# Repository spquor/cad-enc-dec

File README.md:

# cad-enc-dec
Многоканальная система сбора и передачи дифференциальных сигналов

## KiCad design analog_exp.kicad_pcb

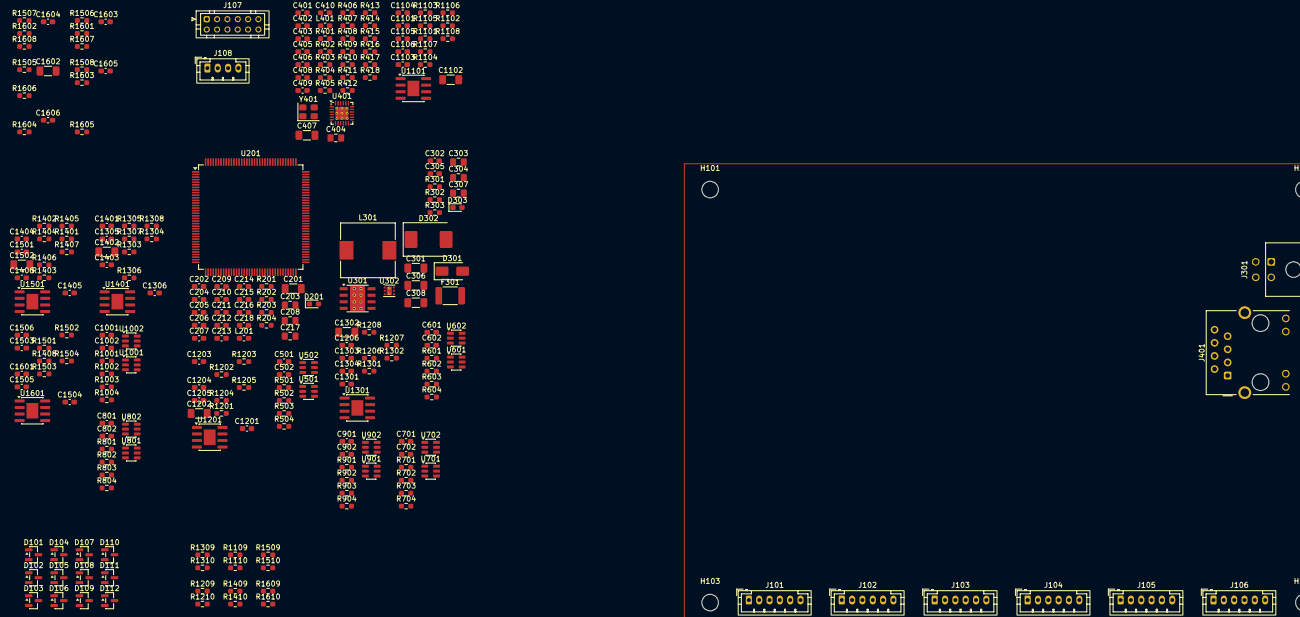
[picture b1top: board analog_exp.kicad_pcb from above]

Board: 2 copper layers, 250 parts (0 on the bottom side), 163 nets, no tracks yet.

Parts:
C201, C301, C407, C1102, C1202, C1302, C1402, C1502, C1602: 10uF; C_1206_3216Metric_Pad1.33x1.80mm_HandSolder
C202, C204, C205, C206, C207, C209, C210, C211, C212, C213, C214, C215, C216, C218, C305, C403, C406, C408, C409, C410, C501, C502, C601, C602, C701, C702, C801, C802, C901, C902, C1001, C1002, C1101, C1103, C1105, C1106, C1201, C1203, C1205, C1206, C1301, C1303, C1305, C1306, C1401, C1403, C1405, C1406, C1501, C1503, C1505, C1506, C1601, C1603, C1605, C1606: 100nF; C_0603_1608Metric_Pad1.08x0.95mm_HandSolder
C203, C208: 2.2uF; C_0805_2012Metric_Pad1.18x1.45mm_HandSolder
C217, C303, C304, C307, C404: 1uF; C_0805_2012Metric_Pad1.18x1.45mm_HandSolder
C302: 220nF; C_0603_1608Metric_Pad1.08x0.95mm_HandSolder
C306, C308: 22uF; C_1206_3216Metric_Pad1.33x1.80mm_HandSolder
C401, C402, C1104, C1204, C1304, C1404, C1504, C1604: 30pF; C_0603_1608Metric_Pad1.08x0.95mm_HandSolder
C405: 470pF; C_0603_1608Metric_Pad1.08x0.95mm_HandSolder
D101, D102, D103, D104, D105, D106, D107, D108, D109, D110, D111, D112: PESD12VL2BT; SOT-23
D201, D303: LED Blue; D_0603_1608Metric_Pad1.05x0.95mm_HandSolder
D301: SMAJ28CA; D_SMA
D302: SS54; D_SMC
F301: Fuse 24V 3A; Fuse_1812_4532Metric_Pad1.30x3.40mm_HandSolder
H101, H102, H103, H104: MountingHole; MountingHole_3.2mm_M3
J101, J102, J103, J104, J105, J106: JST PH B6B; JST_PH_B6B-PH-K_1x06_P2.00mm_Vertical
J107: JST PHD B12B; JST_PHD_B12B-PHDSS_2x06_P2.00mm_Vertical
J108: JST PH B4B; JST_PH_B4B-PH-K_1x04_P2.00mm_Vertical
J301: Power MX 3.0; Molex_Micro-Fit_3.0_43045-0400_2x02_P3.00mm_Horizontal
J401: HR911105A; RJ45_Hanrun_HR911105A_Horizontal
L201, L401: 600R@100Mhz; L_0603_1608Metric_Pad1.05x0.95mm_HandSolder
L301: 2.2uH; L_10.4x10.4_H4.8
R201, R417, R418: 270; R_0603_1608Metric_Pad0.98x0.95mm_HandSolder
R202, R203, R204, R406, R407, R408, R409, R410, R416, R1101, R1102, R1103, R1104, R1106, R1201, R1202, R1203, R1204, R1206, R1301, R1302, R1303, R1304, R1306, R1401, R1402, R1403, R1404, R1406, R1501, R1502, R1503, R1504, R1506, R1601, R1602, R1603, R1604, R1606: 10K; R_0603_1608Metric_Pad0.98x0.95mm_HandSolder
R301, R405: 1K5; R_0603_1608Metric_Pad0.98x0.95mm_HandSolder
R302: 100K; R_0603_1608Metric_Pad0.98x0.95mm_HandSolder
R303: 24K9; R_0603_1608Metric_Pad0.98x0.95mm_HandSolder
R401, R402, R403, R404: 10; R_0603_1608Metric_Pad0.98x0.95mm_HandSolder
R411, R412, R413, R415: 49.9; R_0603_1608Metric_Pad0.98x0.95mm_HandSolder
R414: 12K1; R_0603_1608Metric_Pad0.98x0.95mm_HandSolder
R501, R502, R503, R504, R601, R602, R603, R604, R701, R702, R703, R704, R801, R802, R803, R804, R901, R902, R903, R904, R1001, R1002, R1003, R1004, R1107, R1108, R1207, R1208, R1307, R1308, R1407, R1408, R1507, R1508, R1607, R1608: 0; R_0603_1608Metric_Pad0.98x0.95mm_HandSolder
R1105, R1205, R1305, R1405, R1505, R1605: 30K; R_0603_1608Metric_Pad0.98x0.95mm_HandSolder
R1109, R1110, R1209, R1210, R1309, R1310, R1409, R1410, R1509, R1510, R1609, R1610: 470; R_0603_1608Metric_Pad0.98x0.95mm_HandSolder
U201: STM32H723ZGT; LQFP-144_20x20mm_P0.5mm
U301: LMR33630B; Texas_HSOP-8-1EP_3.9x4.9mm_P1.27mm_ThermalVias
U302: TLV76733; WSON-6-1EP_2x2mm_P0.65mm_EP1x1.6mm_ThermalVias
U401: LAN8742AI; VQFN-24-1EP_4x4mm_P0.5mm_EP2.5x2.5mm_ThermalVias
U501, U502, U601, U602, U701, U702, U801, U802, U901, U902, U1001, U1002: INA600B; SOT-23-6
U1101, U1201, U1301, U1401, U1501, U1601: TSB582; SOIC-8-1EP_3.9x4.9mm_P1.27mm_EP2.29x3mm
Y401: ABM8G-25MHz; Crystal_SMD_3225-4Pin_3.2x2.5mm

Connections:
+3V3: C201.1, C202.1, C204.1, C205.1, C206.1, C207.1, C209.1, C210.1, C211.1, C212.1, C213.1, C214.1, C215.1, C216.1, C307.1, C403.1, D201.2 (A), J108.1, L201.2, L401.1, R202.1, R203.1, R204.1, R405.2, R406.2, R407.2, R408.2, R409.2, R1101.2, R1201.2, R1301.2, R1401.2, R1501.2, R1601.2, U201.6 (VBAT), U201.17 (VDD), U201.30 (VDD), U201.39 (VDD), U201.52 (VDD), U201.62 (VDD), U201.72 (VDD), U201.84 (VDD), U201.95 (VDD33USB), U201.108 (VDD), U201.121 (VDD), U201.131 (VDD), U201.144 (VDD), U302.1 (OUT), U302.2 (SNS), U401.9 (VDDIO)
+5V: C304.1, C306.1, C308.1, C501.2, C502.2, C601.2, C602.2, C701.2, C702.2, C801.2, C802.2, C901.2, C902.2, C1001.2, C1002.2, J107.1, J107.3, J107.5, J107.7, J107.9, J107.11, L301.2, R302.2, U302.4 (EN), U302.6 (IN), U501.6 (V+), U502.6 (V+), U601.6 (V+), U602.6 (V+), U701.6 (V+), U702.6 (V+), U801.6 (V+), U802.6 (V+), U901.6 (V+), U902.6 (V+), U1001.6 (V+), U1002.6 (V+), U1101.3 (+), U1101.5 (+), U1201.3 (+), U1201.5 (+), U1301.3 (+), U1301.5 (+), U1401.3 (+), U1401.5 (+), U1501.3 (+), U1501.5 (+), U1601.3 (+), U1601.5 (+)
+24V: C301.1, C302.1, C1102.2, C1103.2, C1202.2, C1203.2, C1302.2, C1303.2, C1402.2, C1403.2, C1502.2, C1503.2, C1602.2, C1603.2, D302.1 (K), D303.2 (A), F301.2, U301.2 (VIN), U301.3 (EN), U1101.8 (V+), U1201.8 (V+), U1301.8 (V+), U1401.8 (V+), U1501.8 (V+), U1601.8 (V+)
/Ethernet/CRS: R403.1, U201.43 (PA7)
/Ethernet/MDC: R408.1, U201.27 (PC1), U401.13 (MDC)
/Ethernet/MDIO: R405.1, U201.36 (PA2), U401.12 (MDIO)
/Ethernet/REFCLK: R404.1, U201.35 (PA1)
/Ethernet/RXD0: R401.1, U201.44 (PC4)
/Ethernet/RXD1: R402.1, U201.45 (PC5)
/Ethernet/TXD0: U201.73 (PB12), U401.17 (TXD0)
/Ethernet/TXD1: U201.74 (PB13), U401.18 (TXD1)
/Ethernet/TXEN: U201.70 (PB11), U401.16 (TXEN)
/Ethernet/nRST: U201.69 (PB10), U401.15 (~RST)
/GENOUT: C1101.1, C1201.1, C1301.1, C1401.1, C1501.1, C1601.1, R1101.1, R1102.2, R1201.1, R1202.2, R1301.1, R1302.2, R1401.1, R1402.2, R1501.1, R1502.2, R1601.1, R1602.2, U201.41 (PA5)
/RE1_COS: U201.20 (PF8), U502.1
/RE1_COS+: D102.1 (A1), J101.5, R503.1
/RE1_COS-: D102.2 (A2), J101.6, R504.1
/RE1_EXC+: J101.1, R1107.2, R1109.2
/RE1_EXC-: J101.2, R1108.2, R1110.2
/RE1_SIN: U201.19 (PF7), U501.1
/RE1_SIN+: D101.1 (A1), J101.3, R501.1
/RE1_SIN-: D101.2 (A2), J101.4, R502.1
/RE2_COS: U201.22 (PF10), U602.1
/RE2_COS+: D104.1 (A1), J102.5, R603.1
/RE2_COS-: D104.2 (A2), J102.6, R604.1
/RE2_EXC+: J102.1, R1207.2, R1209.2
/RE2_EXC-: J102.2, R1208.2, R1210.2
/RE2_SIN: U201.21 (PF9), U601.1
/RE2_SIN+: D103.1 (A1), J102.3, R601.1
/RE2_SIN-: D103.2 (A2), J102.4, R602.1
/RE3_COS: U201.26 (PC0), U702.1
/RE3_COS+: D106.1 (A1), J103.5, R703.1
/RE3_COS-: D106.2 (A2), J103.6, R704.1
/RE3_EXC+: J103.1, R1307.2, R1309.2
/RE3_EXC-: J103.2, R1308.2, R1310.2
/RE3_SIN: U201.34 (PA0), U701.1
/RE3_SIN+: D105.1 (A1), J103.3, R701.1
/RE3_SIN-: D105.2 (A2), J103.4, R702.1
/RE4_COS: U201.40 (PA4), U802.1
/RE4_COS+: D108.1 (A1), J104.5, R803.1
/RE4_COS-: D108.2 (A2), J104.6, R804.1
/RE4_EXC+: J104.1, R1407.2, R1409.2
/RE4_EXC-: J104.2, R1408.2, R1410.2
/RE4_SIN: U201.37 (PA3), U801.1
/RE4_SIN+: D107.1 (A1), J104.3, R801.1
/RE4_SIN-: D107.2 (A2), J104.4, R802.1
/RE5_COS: U201.47 (PB1), U902.1
/RE5_COS+: D110.1 (A1), J105.5, R903.1
/RE5_COS-: D110.2 (A2), J105.6, R904.1
/RE5_EXC+: J105.1, R1507.2, R1509.2
/RE5_EXC-: J105.2, R1508.2, R1510.2
/RE5_SIN: U201.46 (PB0), U901.1
/RE5_SIN+: D109.1 (A1), J105.3, R901.1
/RE5_SIN-: D109.2 (A2), J105.4, R902.1
/RE6_COS: U201.54 (PF14), U1002.1
/RE6_COS+: D112.1 (A1), J106.5, R1003.1
/RE6_COS-: D112.2 (A2), J106.6, R1004.1
/RE6_EXC+: J106.1, R1607.2, R1609.2
/RE6_EXC-: J106.2, R1608.2, R1610.2
/RE6_SIN: U201.53 (PF13), U1001.1
/RE6_SIN+: D111.1 (A1), J106.3, R1001.1
/RE6_SIN-: D111.2 (A2), J106.4, R1002.1
/SWDCLK: J108.2, U201.109 (PA14(JTCK)
/SWDIO: J108.3, U201.105 (PA13(JTMS)
/VREFOUT: U201.32 (VREF+), U501.5 (REF), U502.5 (REF), U601.5 (REF), U602.5 (REF), U701.5 (REF), U702.5 (REF), U801.5 (REF), U802.5 (REF), U901.5 (REF), U902.5 (REF), U1001.5 (REF), U1002.5 (REF)
GND: C201.2, C202.2, C203.2, C204.2, C205.2, C206.2, C207.2, C208.2, C209.2, C210.2, C211.2, C212.2, C213.2, C214.2, C215.2, C216.2, C217.2, C218.2, C301.2, C302.2, C303.2, C304.2, C306.2, C307.2, C308.2, C401.1, C402.1, C403.2, C404.2, C405.2, C406.2, C407.2, C408.2, C409.2, C410.2, C501.1, C502.1, C601.1, C602.1, C701.1, C702.1, C801.1, C802.1, C901.1, C902.1, C1001.1, C1002.1, C1102.1, C1103.1, C1105.1, C1106.1, C1202.1, C1203.1, C1205.1, C1206.1, C1302.1, C1303.1, C1305.1, C1306.1, C1402.1, C1403.1, C1405.1, C1406.1, C1502.1, C1503.1, C1505.1, C1506.1, C1602.1, C1603.1, C1605.1, C1606.1, D101.3 (common), D102.3 (common), D103.3 (common), D104.3 (common), D105.3 (common), D106.3 (common), D107.3 (common), D108.3 (common), D109.3 (common), D110.3 (common), D111.3 (common), D112.3 (common), D301.1 (A1), D302.2 (A), J107.2, J107.4, J107.6, J107.8, J107.10, J107.12, J108.4, J301.3, J301.4, J401.8, J401.SH, R201.1, R301.1, R303.1, R410.1, R414.1, R416.1, R417.1, R418.1, R1102.1, R1202.1, R1302.1, R1402.1, R1502.1, R1602.1, U201.16 (VSS), U201.31 (VSSA), U201.38 (VSS), U201.51 (VSS), U201.61 (VSS), U201.83 (VSS), U201.94 (VSS), U201.107 (VSS), U201.120 (VSS), U201.130 (VSS), U301.1 (GND), U301.9 (GND), U302.3 (GND), U302.5 (GND), U302.7 (PAD), U401.25 (VSS), U501.2 (GND), U502.2 (GND), U601.2 (GND), U602.2 (GND), U701.2 (GND), U702.2 (GND), U801.2 (GND), U802.2 (GND), U901.2 (GND), U902.2 (GND), U1001.2 (GND), U1002.2 (GND), U1101.4 (V-), U1201.4 (V-), U1301.4 (V-), U1401.4 (V-), U1501.4 (V-), U1601.4 (V-), Y401.2 (G), Y401.4 (G)
unnamed: C203.1, U201.71 (VCAP)
unnamed: C208.1, U201.106 (VCAP)
unnamed: C1101.2, R1103.1
unnamed: C1104.2, R1104.1, R1105.2, R1107.1, U1101.1
unnamed: C1105.2, R1109.1
unnamed: C1106.2, R1110.1
unnamed: C1201.2, R1203.1
unnamed: C1204.2, R1204.1, R1205.2, R1207.1, U1201.1
unnamed: C1205.2, R1209.1
unnamed: C1206.2, R1210.1
unnamed: C1301.2, R1303.1
unnamed: C1304.2, R1304.1, R1305.2, R1307.1, U1301.1
unnamed: C1305.2, R1309.1
unnamed: C1306.2, R1310.1
unnamed: C1401.2, R1403.1
unnamed: C1404.2, R1404.1, R1405.2, R1407.1, U1401.1
unnamed: C1405.2, R1409.1
unnamed: C1406.2, R1410.1
unnamed: C1501.2, R1503.1
unnamed: C1504.2, R1504.1, R1505.2, R1507.1, U1501.1
unnamed: C1505.2, R1509.1
unnamed: C1506.2, R1510.1
unnamed: C1601.2, R1603.1
unnamed: C1604.2, R1604.1, R1605.2, R1607.1, U1601.1
unnamed: C1605.2, R1609.1
unnamed: C1606.2, R1610.1
unnamed: D201.1 (K), R201.2
unnamed: D303.1 (K), R301.2
unnamed: J401.10, R417.2
unnamed: J401.11, R418.2
unnamed: C406.1, C407.1, C408.1, C409.1, C410.1, J401.4 (TCT), J401.5 (RCT), L401.2, R411.2, R412.2, R413.2, R415.2, U401.1 (VDD2A), U401.19 (VDD1A)
unnamed: J401.3 (RD+), R413.1, U401.23 (RXP)
unnamed: J401.6 (RD-), R415.1, U401.22 (RXN)
unnamed: J401.1 (TD+), R411.1, U401.21 (TXP)
unnamed: J401.2 (TD-), R412.1, U401.20 (TXN)
unnamed: R1106.2, R1108.1, U1101.7
unnamed: R1206.2, R1208.1, U1201.7
unnamed: R1306.2, R1308.1, U1301.7
unnamed: R1406.2, R1408.1, U1401.7
unnamed: R1506.2, R1508.1, U1501.7
unnamed: R1606.2, R1608.1, U1601.7
unnamed: R203.2, U201.138 (BOOT0)
unnamed: R202.2, U201.25 (NRST)
unnamed: R204.2, U201.143 (PDR_ON)
unnamed: C217.1, C218.1, L201.1, U201.33 (VDDA)
unnamed: C305.1, U301.7 (BOOT)
unnamed: R302.1, R303.2, U301.5 (FB)
unnamed: C305.2, L301.1, U301.8 (SW)
unnamed: C303.1, U301.6 (VCC)
unnamed: R403.2, U401.11 (CRS_DV/MODE2)
unnamed: J401.12, U401.3 (LED1/REGOFF)
unnamed: J401.9, R416.2, U401.2 (LED2/~INTSEL)
unnamed: R414.2, U401.24 (RBIAS)
unnamed: R401.2, R406.1, U401.8 (RXD0/MODE0)
unnamed: R402.2, R407.1, U401.7 (RXD1/MODE1)
unnamed: R410.2, U401.10 (RXER/PHYAD0)
unnamed: C404.1, C405.1, U401.6 (VDDCR)
unnamed: C401.2, U401.5 (XTAL1/CLKIN), Y401.3
unnamed: C402.2, U401.4 (XTAL2), Y401.1
unnamed: R404.2, R409.1, U401.14 (~INT/REFCLKO)
unnamed: R501.2, U501.3 (+)
unnamed: R502.2, U501.4 (-)
unnamed: R503.2, U502.3 (+)
unnamed: R504.2, U502.4 (-)
unnamed: R601.2, U601.3 (+)
unnamed: R602.2, U601.4 (-)
unnamed: R603.2, U602.3 (+)
unnamed: R604.2, U602.4 (-)
unnamed: R701.2, U701.3 (+)
unnamed: R702.2, U701.4 (-)
unnamed: R703.2, U702.3 (+)
unnamed: R704.2, U702.4 (-)
unnamed: R801.2, U801.3 (+)
unnamed: R802.2, U801.4 (-)
unnamed: R803.2, U802.3 (+)
unnamed: R804.2, U802.4 (-)
unnamed: R901.2, U901.3 (+)
unnamed: R902.2, U901.4 (-)
unnamed: R903.2, U902.3 (+)
unnamed: R904.2, U902.4 (-)
unnamed: R1001.2, U1001.3 (+)
unnamed: R1002.2, U1001.4 (-)
unnamed: R1003.2, U1002.3 (+)
unnamed: R1004.2, U1002.4 (-)
unnamed: C1104.1, R1103.2, R1105.1, U1101.2 (-)
unnamed: R1104.2, R1106.1, U1101.6 (-)
unnamed: C1204.1, R1203.2, R1205.1, U1201.2 (-)
unnamed: R1204.2, R1206.1, U1201.6 (-)
unnamed: C1304.1, R1303.2, R1305.1, U1301.2 (-)
unnamed: R1304.2, R1306.1, U1301.6 (-)
unnamed: C1404.1, R1403.2, R1405.1, U1401.2 (-)
unnamed: R1404.2, R1406.1, U1401.6 (-)
unnamed: C1504.1, R1503.2, R1505.1, U1501.2 (-)
unnamed: R1504.2, R1506.1, U1501.6 (-)
unnamed: C1604.1, R1603.2, R1605.1, U1601.2 (-)
unnamed: R1604.2, R1606.1, U1601.6 (-)
VDD: D301.2 (A2), F301.1, J301.1, J301.2

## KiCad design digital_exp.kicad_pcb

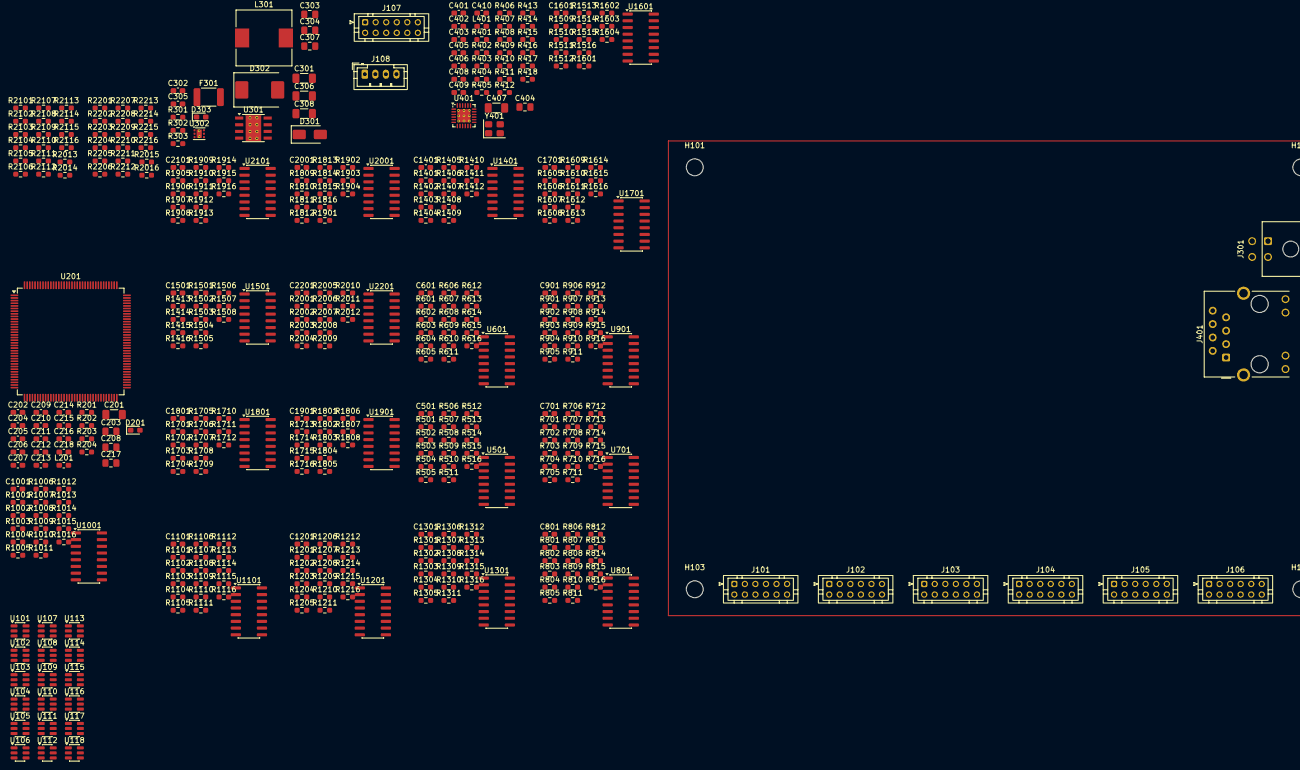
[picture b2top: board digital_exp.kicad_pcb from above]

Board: 2 copper layers, 430 parts (0 on the bottom side), 371 nets, no tracks yet.

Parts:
C201, C301, C407: 10uF; C_1206_3216Metric_Pad1.33x1.80mm_HandSolder
C202, C204, C205, C206, C207, C209, C210, C211, C212, C213, C214, C215, C216, C218, C305, C403, C406, C408, C409, C410, C501, C601, C701, C801, C901, C1001, C1101, C1201, C1301, C1401, C1501, C1601, C1701, C1801, C1901, C2001, C2101, C2201: 100nF; C_0603_1608Metric_Pad1.08x0.95mm_HandSolder
C203, C208: 2.2uF; C_0805_2012Metric_Pad1.18x1.45mm_HandSolder
C217, C303, C304, C307, C404: 1uF; C_0805_2012Metric_Pad1.18x1.45mm_HandSolder
C302: 220nF; C_0603_1608Metric_Pad1.08x0.95mm_HandSolder
C306, C308: 22uF; C_1206_3216Metric_Pad1.33x1.80mm_HandSolder
C401, C402: 30pF; C_0603_1608Metric_Pad1.08x0.95mm_HandSolder
C405: 470pF; C_0603_1608Metric_Pad1.08x0.95mm_HandSolder
D201, D303: LED Blue; D_0603_1608Metric_Pad1.05x0.95mm_HandSolder
D301: SMAJ28CA; D_SMA
D302: SS54; D_SMC
F301: Fuse 24V 3A; Fuse_1812_4532Metric_Pad1.30x3.40mm_HandSolder
H101, H102, H103, H104: MountingHole; MountingHole_3.2mm_M3
J101, J102, J103, J104, J105, J106, J107: JST PHD B12B; JST_PHD_B12B-PHDSS_2x06_P2.00mm_Vertical
J108: JST PH B4B; JST_PH_B4B-PH-K_1x04_P2.00mm_Vertical
J301: Power MX 3.0; Molex_Micro-Fit_3.0_43045-0400_2x02_P3.00mm_Horizontal
J401: HR911105A; RJ45_Hanrun_HR911105A_Horizontal
L201, L401: 600R@100Mhz; L_0603_1608Metric_Pad1.05x0.95mm_HandSolder
L301: 2.2uH; L_10.4x10.4_H4.8
R201, R417, R418: 270; R_0603_1608Metric_Pad0.98x0.95mm_HandSolder
R202, R203, R204, R406, R407, R408, R409, R410, R416, R1401, R1402, R1403, R1404, R1501, R1502, R1503, R1504, R1601, R1602, R1603, R1604, R1701, R1702, R1703, R1704, R1801, R1802, R1803, R1804, R1901, R1902, R1903, R1904, R2001, R2002, R2003, R2004, R2101, R2102, R2103, R2104, R2201, R2202, R2203, R2204: 10K; R_0603_1608Metric_Pad0.98x0.95mm_HandSolder
R301, R405: 1K5; R_0603_1608Metric_Pad0.98x0.95mm_HandSolder
R302: 100K; R_0603_1608Metric_Pad0.98x0.95mm_HandSolder
R303: 24K9; R_0603_1608Metric_Pad0.98x0.95mm_HandSolder
R401, R402, R403, R404, R505, R506, R507, R508, R509, R510, R511, R512, R605, R606, R607, R608, R609, R610, R611, R612, R705, R706, R707, R708, R709, R710, R711, R712, R805, R806, R807, R808, R809, R810, R811, R812, R905, R906, R907, R908, R909, R910, R911, R912, R1005, R1006, R1007, R1008, R1009, R1010, R1011, R1012, R1105, R1106, R1107, R1108, R1109, R1110, R1111, R1112, R1205, R1206, R1207, R1208, R1209, R1210, R1211, R1212, R1305, R1306, R1307, R1308, R1309, R1310, R1311, R1312, R1409, R1410, R1411, R1412, R1413, R1414, R1415, R1416, R1509, R1510, R1511, R1512, R1513, R1514, R1515, R1516, R1609, R1610, R1611, R1612, R1613, R1614, R1615, R1616, R1709, R1710, R1711, R1712, R1713, R1714, R1715, R1716, R1809, R1810, R1811, R1812, R1813, R1814, R1815, R1816, R1909, R1910, R1911, R1912, R1913, R1914, R1915, R1916, R2009, R2010, R2011, R2012, R2013, R2014, R2015, R2016, R2109, R2110, R2111, R2112, R2113, R2114, R2115, R2116, R2209, R2210, R2211, R2212, R2213, R2214, R2215, R2216: 10; R_0603_1608Metric_Pad0.98x0.95mm_HandSolder
R411, R412, R413, R415: 49.9; R_0603_1608Metric_Pad0.98x0.95mm_HandSolder
R414: 12K1; R_0603_1608Metric_Pad0.98x0.95mm_HandSolder
R501, R502, R503, R504, R601, R602, R603, R604, R701, R702, R703, R704, R801, R802, R803, R804, R901, R902, R903, R904, R1001, R1002, R1003, R1004, R1101, R1102, R1103, R1104, R1201, R1202, R1203, R1204, R1301, R1302, R1303, R1304: 100; R_0603_1608Metric_Pad0.98x0.95mm_HandSolder
R513, R514, R515, R516, R613, R614, R615, R616, R713, R714, R715, R716, R813, R814, R815, R816, R913, R914, R915, R916, R1013, R1014, R1015, R1016, R1113, R1114, R1115, R1116, R1213, R1214, R1215, R1216, R1313, R1314, R1315, R1316, R1405, R1406, R1407, R1408, R1505, R1506, R1507, R1508, R1605, R1606, R1607, R1608, R1705, R1706, R1707, R1708, R1805, R1806, R1807, R1808, R1905, R1906, R1907, R1908, R2005, R2006, R2007, R2008, R2105, R2106, R2107, R2108, R2205, R2206, R2207, R2208: 0R; R_0603_1608Metric_Pad0.98x0.95mm_HandSolder
U101, U102, U103, U104, U105, U106, U107, U108, U109, U110, U111, U112, U113, U114, U115, U116, U117, U118: SRV05-4; SOT-23-6
U201: STM32H723ZGT; LQFP-144_20x20mm_P0.5mm
U301: LMR33630B; Texas_HSOP-8-1EP_3.9x4.9mm_P1.27mm_ThermalVias
U302: TLV76733; WSON-6-1EP_2x2mm_P0.65mm_EP1x1.6mm_ThermalVias
U401: LAN8742AI; VQFN-24-1EP_4x4mm_P0.5mm_EP2.5x2.5mm_ThermalVias
U501, U601, U701, U801, U901, U1001, U1101, U1201, U1301: AM26LV32E; SOIC-16_3.9x9.9mm_P1.27mm
U1401, U1501, U1601, U1701, U1801, U1901, U2001, U2101, U2201: AM26LV31E; SOIC-16_3.9x9.9mm_P1.27mm
Y401: ABM8G-25MHz; Crystal_SMD_3225-4Pin_3.2x2.5mm

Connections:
+3V3: C201.1, C202.1, C204.1, C205.1, C206.1, C207.1, C209.1, C210.1, C211.1, C212.1, C213.1, C214.1, C215.1, C216.1, C307.1, C403.1, C501.2, C601.2, C701.2, C801.2, C901.2, C1001.2, C1101.2, C1201.2, C1301.2, C1401.2, C1501.2, C1601.2, C1701.2, C1801.2, C1901.2, C2001.2, C2101.2, C2201.2, D201.2 (A), J108.1, L201.2, L401.1, R202.1, R203.1, R204.1, R405.2, R406.2, R407.2, R408.2, R409.2, U201.6 (VBAT), U201.17 (VDD), U201.30 (VDD), U201.39 (VDD), U201.52 (VDD), U201.62 (VDD), U201.72 (VDD), U201.84 (VDD), U201.95 (VDD33USB), U201.108 (VDD), U201.121 (VDD), U201.131 (VDD), U201.144 (VDD), U302.1 (OUT), U302.2 (SNS), U401.9 (VDDIO), U501.4 (G), U501.16 (VDD), U601.4 (G), U601.16 (VDD), U701.4 (G), U701.16 (VDD), U801.4 (G), U801.16 (VDD), U901.4 (G), U901.16 (VDD), U1001.4 (G), U1001.16 (VDD), U1101.4 (G), U1101.16 (VDD), U1201.4 (G), U1201.16 (VDD), U1301.4 (G), U1301.16 (VDD), U1401.4 (G), U1401.16 (VDD), U1501.4 (G), U1501.16 (VDD), U1601.4 (G), U1601.16 (VDD), U1701.4 (G), U1701.16 (VDD), U1801.4 (G), U1801.16 (VDD), U1901.4 (G), U1901.16 (VDD), U2001.4 (G), U2001.16 (VDD), U2101.4 (G), U2101.16 (VDD), U2201.4 (G), U2201.16 (VDD)
+5V: C304.1, C306.1, C308.1, J107.1, J107.3, J107.5, J107.7, J107.9, J107.11, L301.2, R302.2, U302.4 (EN), U302.6 (IN)
+24V: C301.1, C302.1, D302.1 (K), D303.2 (A), F301.2, U301.2 (VIN), U301.3 (EN)
/EN1_A: R513.2, R1401.2, R1405.1, U201.15 (PF5)
/EN1_A+: J101.1, R501.1, R505.1, R1409.2, U101.1 (IO1)
/EN1_A-: J101.2, R501.2, R506.1, R1410.2, U101.4 (IO3)
/EN1_B: R514.2, R1402.2, R1406.1, U201.14 (PF4)
/EN1_B+: J101.3, R502.1, R507.1, R1411.2, U101.3 (IO2)
/EN1_B-: J101.4, R502.2, R508.1, R1412.2, U101.6 (IO4)
/EN1_U: R516.2, R1404.2, R1408.1, U201.12 (PF2)
/EN1_U+: J101.7, R504.1, R511.1, R1415.2, U110.3 (IO2)
/EN1_U-: J101.8, R504.2, R512.1, R1416.2, U110.6 (IO4)
/EN1_V: R613.2, R1501.2, R1505.1, U201.11 (PF1)
/EN1_V+: J101.9, R601.1, R605.1, R1509.2, U102.1 (IO1)
/EN1_V-: J101.10, R601.2, R606.1, R1510.2, U102.4 (IO3)
/EN1_W: R614.2, R1502.2, R1506.1, U201.10 (PF0)
/EN1_W+: J101.11, R602.1, R607.1, R1511.2, U102.3 (IO2)
/EN1_W-: J101.12, R602.2, R608.1, R1512.2, U102.6 (IO4)
/EN1_Z: R515.2, R1403.2, R1407.1, U201.13 (PF3)
/EN1_Z+: J101.5, R503.1, R509.1, R1413.2, U110.1 (IO1)
/EN1_Z-: J101.6, R503.2, R510.1, R1414.2, U110.4 (IO3)
/EN2_A: R615.2, R1503.2, R1507.1, U201.59 (PE8)
/EN2_A+: J102.1, R603.1, R609.1, R1513.2, U111.1 (IO1)
/EN2_A-: J102.2, R603.2, R610.1, R1514.2, U111.4 (IO3)
/EN2_B: R616.2, R1504.2, R1508.1, U201.63 (PE10)
/EN2_B+: J102.3, R604.1, R611.1, R1515.2, U111.3 (IO2)
/EN2_B-: J102.4, R604.2, R612.1, R1516.2, U111.6 (IO4)
/EN2_U: R714.2, R1602.2, R1606.1, U201.66 (PE13)
/EN2_U+: J102.7, R702.1, R707.1, R1611.2, U103.3 (IO2)
/EN2_U-: J102.8, R702.2, R708.1, R1612.2, U103.6 (IO4)
/EN2_V: R715.2, R1603.2, R1607.1, U201.60 (PE9)
/EN2_V+: J102.9, R703.1, R709.1, R1613.2, U112.1 (IO1)
/EN2_V-: J102.10, R703.2, R710.1, R1614.2, U112.4 (IO3)
/EN2_W: R716.2, R1604.2, R1608.1, U201.64 (PE11)
/EN2_W+: J102.11, R704.1, R711.1, R1615.2, U112.3 (IO2)
/EN2_W-: J102.12, R704.2, R712.1, R1616.2, U112.6 (IO4)
/EN2_Z: R713.2, R1601.2, R1605.1, U201.65 (PE12)
/EN2_Z+: J102.5, R701.1, R705.1, R1609.2, U103.1 (IO1)
/EN2_Z-: J102.6, R701.2, R706.1, R1610.2, U103.4 (IO3)
/EN3_A: R813.2, R1701.2, R1705.1, U201.77 (PD8)
/EN3_A+: J103.1, R801.1, R805.1, R1709.2, U104.1 (IO1)
/EN3_A-: J103.2, R801.2, R806.1, R1710.2, U104.4 (IO3)
/EN3_B: R814.2, R1702.2, R1706.1, U201.78 (PD9)
/EN3_B+: J103.3, R802.1, R807.1, R1711.2, U104.3 (IO2)
/EN3_B-: J103.4, R802.2, R808.1, R1712.2, U104.6 (IO4)
/EN3_U: R816.2, R1704.2, R1708.1, U201.80 (PD11)
/EN3_U+: J103.7, R804.1, R811.1, R1715.2, U113.3 (IO2)
/EN3_U-: J103.8, R804.2, R812.1, R1716.2, U113.6 (IO4)
/EN3_V: R913.2, R1801.2, R1805.1, U201.81 (PD12)
/EN3_V+: J103.9, R901.1, R905.1, R1809.2, U105.1 (IO1)
/EN3_V-: J103.10, R901.2, R906.1, R1810.2, U105.4 (IO3)
/EN3_W: R914.2, R1802.2, R1806.1, U201.82 (PD13)
/EN3_W+: J103.11, R902.1, R907.1, R1811.2, U105.3 (IO2)
/EN3_W-: J103.12, R902.2, R908.1, R1812.2, U105.6 (IO4)
/EN3_Z: R815.2, R1703.2, R1707.1, U201.79 (PD10)
/EN3_Z+: J103.5, R803.1, R809.1, R1713.2, U113.1 (IO1)
/EN3_Z-: J103.6, R803.2, R810.1, R1714.2, U113.4 (IO3)
/EN4_A: R915.2, R1803.2, R1807.1, U201.90 (PG5)
/EN4_A+: J104.1, R903.1, R909.1, R1813.2, U114.1 (IO1)
/EN4_A-: J104.2, R903.2, R910.1, R1814.2, U114.4 (IO3)
/EN4_B: R916.2, R1804.2, R1808.1, U201.91 (PG6)
/EN4_B+: J104.3, R904.1, R911.1, R1815.2, U114.3 (IO2)
/EN4_B-: J104.4, R904.2, R912.1, R1816.2, U114.6 (IO4)
/EN4_U: R1014.2, R1902.2, R1906.1, U201.93 (PG8)
/EN4_U+: J104.7, R1002.1, R1007.1, R1911.2, U106.3 (IO2)
/EN4_U-: J104.8, R1002.2, R1008.1, R1912.2, U106.6 (IO4)
/EN4_V: R1015.2, R1903.2, R1907.1, U201.96 (PC6)
/EN4_V+: J104.9, R1003.1, R1009.1, R1913.2, U115.1 (IO1)
/EN4_V-: J104.10, R1003.2, R1010.1, R1914.2, U115.4 (IO3)
/EN4_W: R1016.2, R1904.2, R1908.1, U201.97 (PC7)
/EN4_W+: J104.11, R1004.1, R1011.1, R1915.2, U115.3 (IO2)
/EN4_W-: J104.12, R1004.2, R1012.1, R1916.2, U115.6 (IO4)
/EN4_Z: R1013.2, R1901.2, R1905.1, U201.92 (PG7)
/EN4_Z+: J104.5, R1001.1, R1005.1, R1909.2, U106.1 (IO1)
/EN4_Z-: J104.6, R1001.2, R1006.1, R1910.2, U106.4 (IO3)
/EN5_A: R1113.2, R2001.2, R2005.1, U201.111 (PC10)
/EN5_A+: J105.1, R1101.1, R1105.1, R2009.2, U107.1 (IO1)
/EN5_A-: J105.2, R1101.2, R1106.1, R2010.2, U107.4 (IO3)
/EN5_B: R1114.2, R2002.2, R2006.1, U201.112 (PC11)
/EN5_B+: J105.3, R1102.1, R1107.1, R2011.2, U107.3 (IO2)
/EN5_B-: J105.4, R1102.2, R1108.1, R2012.2, U107.6 (IO4)
/EN5_U: R1116.2, R2004.2, R2008.1, U201.115 (PD1)
/EN5_U+: J105.7, R1104.1, R1111.1, R2015.2, U116.3 (IO2)
/EN5_U-: J105.8, R1104.2, R1112.1, R2016.2, U116.6 (IO4)
/EN5_V: R1213.2, R2101.2, R2105.1, U201.110 (PA15(JTDI))
/EN5_V+: J105.9, R1201.1, R1205.1, R2109.2, U108.1 (IO1)
/EN5_V-: J105.10, R1201.2, R1206.1, R2110.2, U108.4 (IO3)
/EN5_W: R1214.2, R2102.2, R2106.1, U201.133 (PB3(JTDO)
/EN5_W+: J105.11, R1202.1, R1207.1, R2111.2, U108.3 (IO2)
/EN5_W-: J105.12, R1202.2, R1208.1, R2112.2, U108.6 (IO4)
/EN5_Z: R1115.2, R2003.2, R2007.1, U201.114 (PD0)
/EN5_Z+: J105.5, R1103.1, R1109.1, R2013.2, U116.1 (IO1)
/EN5_Z-: J105.6, R1103.2, R1110.1, R2014.2, U116.4 (IO3)
/EN6_A: R1215.2, R2103.2, R2107.1, U201.125 (PG10)
/EN6_A+: J106.1, R1203.1, R1209.1, R2113.2, U117.1 (IO1)
/EN6_A-: J106.2, R1203.2, R1210.1, R2114.2, U117.4 (IO3)
/EN6_B: R1216.2, R2104.2, R2108.1, U201.126 (PG11)
/EN6_B+: J106.3, R1204.1, R1211.1, R2115.2, U117.3 (IO2)
/EN6_B-: J106.4, R1204.2, R1212.1, R2116.2, U117.6 (IO4)
/EN6_U: R1314.2, R2202.2, R2206.1, U201.128 (PG13)
/EN6_U+: J106.7, R1302.1, R1307.1, R2211.2, U109.3 (IO2)
/EN6_U-: J106.8, R1302.2, R1308.1, R2212.2, U109.6 (IO4)
/EN6_V: R1315.2, R2203.2, R2207.1, U201.134 (PB4(NJTRST))
/EN6_V+: J106.9, R1303.1, R1309.1, R2213.2, U118.1 (IO1)
/EN6_V-: J106.10, R1303.2, R1310.1, R2214.2, U118.4 (IO3)
/EN6_W: R1316.2, R2204.2, R2208.1, U201.135 (PB5)
/EN6_W+: J106.11, R1304.1, R1311.1, R2215.2, U118.3 (IO2)
/EN6_W-: J106.12, R1304.2, R1312.1, R2216.2, U118.6 (IO4)
/EN6_Z: R1313.2, R2201.2, R2205.1, U201.127 (PG12)
/EN6_Z+: J106.5, R1301.1, R1305.1, R2209.2, U109.1 (IO1)
/EN6_Z-: J106.6, R1301.2, R1306.1, R2210.2, U109.4 (IO3)
/Ethernet/CRS: R403.1, U201.43 (PA7)
/Ethernet/MDC: R408.1, U201.27 (PC1), U401.13 (MDC)
/Ethernet/MDIO: R405.1, U201.36 (PA2), U401.12 (MDIO)
/Ethernet/REFCLK: R404.1, U201.35 (PA1)
/Ethernet/RXD0: R401.1, U201.44 (PC4)
/Ethernet/RXD1: R402.1, U201.45 (PC5)
/Ethernet/TXD0: U201.73 (PB12), U401.17 (TXD0)
/Ethernet/TXD1: U201.74 (PB13), U401.18 (TXD1)
/Ethernet/TXEN: U201.70 (PB11), U401.16 (TXEN)
/Ethernet/nRST: U201.69 (PB10), U401.15 (~RST)
/SWDCLK: J108.2, U201.109 (PA14(JTCK)
/SWDIO: J108.3, U201.105 (PA13(JTMS)
GND: C201.2, C202.2, C203.2, C204.2, C205.2, C206.2, C207.2, C208.2, C209.2, C210.2, C211.2, C212.2, C213.2, C214.2, C215.2, C216.2, C217.2, C218.2, C301.2, C302.2, C303.2, C304.2, C306.2, C307.2, C308.2, C401.1, C402.1, C403.2, C404.2, C405.2, C406.2, C407.2, C408.2, C409.2, C410.2, C501.1, C601.1, C701.1, C801.1, C901.1, C1001.1, C1101.1, C1201.1, C1301.1, C1401.1, C1501.1, C1601.1, C1701.1, C1801.1, C1901.1, C2001.1, C2101.1, C2201.1, D301.1 (A1), D302.2 (A), J107.2, J107.4, J107.6, J107.8, J107.10, J107.12, J108.4, J301.3, J301.4, J401.8, J401.SH, R201.1, R301.1, R303.1, R410.1, R414.1, R416.1, R417.1, R418.1, R1401.1, R1402.1, R1403.1, R1404.1, R1501.1, R1502.1, R1503.1, R1504.1, R1601.1, R1602.1, R1603.1, R1604.1, R1701.1, R1702.1, R1703.1, R1704.1, R1801.1, R1802.1, R1803.1, R1804.1, R1901.1, R1902.1, R1903.1, R1904.1, R2001.1, R2002.1, R2003.1, R2004.1, R2101.1, R2102.1, R2103.1, R2104.1, R2201.1, R2202.1, R2203.1, R2204.1, U101.2 (VN), U102.2 (VN), U103.2 (VN), U104.2 (VN), U105.2 (VN), U106.2 (VN), U107.2 (VN), U108.2 (VN), U109.2 (VN), U110.2 (VN), U111.2 (VN), U112.2 (VN), U113.2 (VN), U114.2 (VN), U115.2 (VN), U116.2 (VN), U117.2 (VN), U118.2 (VN), U201.16 (VSS), U201.31 (VSSA), U201.38 (VSS), U201.51 (VSS), U201.61 (VSS), U201.83 (VSS), U201.94 (VSS), U201.107 (VSS), U201.120 (VSS), U201.130 (VSS), U301.1 (GND), U301.9 (GND), U302.3 (GND), U302.5 (GND), U302.7 (PAD), U401.25 (VSS), U501.8 (GND), U501.12 (~G), U601.8 (GND), U601.12 (~G), U701.8 (GND), U701.12 (~G), U801.8 (GND), U801.12 (~G), U901.8 (GND), U901.12 (~G), U1001.8 (GND), U1001.12 (~G), U1101.8 (GND), U1101.12 (~G), U1201.8 (GND), U1201.12 (~G), U1301.8 (GND), U1301.12 (~G), U1401.8 (GND), U1401.12 (~G), U1501.8 (GND), U1501.12 (~G), U1601.8 (GND), U1601.12 (~G), U1701.8 (GND), U1701.12 (~G), U1801.8 (GND), U1801.12 (~G), U1901.8 (GND), U1901.12 (~G), U2001.8 (GND), U2001.12 (~G), U2101.8 (GND), U2101.12 (~G), U2201.8 (GND), U2201.12 (~G), Y401.2 (G), Y401.4 (G)
unnamed: C203.1, U201.71 (VCAP)
unnamed: C208.1, U201.106 (VCAP)
unnamed: D201.1 (K), R201.2
unnamed: D303.1 (K), R301.2
unnamed: J401.10, R417.2
unnamed: J401.11, R418.2
unnamed: C406.1, C407.1, C408.1, C409.1, C410.1, J401.4 (TCT), J401.5 (RCT), L401.2, R411.2, R412.2, R413.2, R415.2, U401.1 (VDD2A), U401.19 (VDD1A)
unnamed: J401.3 (RD+), R413.1, U401.23 (RXP)
unnamed: J401.6 (RD-), R415.1, U401.22 (RXN)
unnamed: J401.1 (TD+), R411.1, U401.21 (TXP)
unnamed: J401.2 (TD-), R412.1, U401.20 (TXN)
unnamed: R203.2, U201.138 (BOOT0)
unnamed: R202.2, U201.25 (NRST)
unnamed: R204.2, U201.143 (PDR_ON)
unnamed: C217.1, C218.1, L201.1, U201.33 (VDDA)
unnamed: C305.1, U301.7 (BOOT)
unnamed: R302.1, R303.2, U301.5 (FB)
unnamed: C305.2, L301.1, U301.8 (SW)
unnamed: C303.1, U301.6 (VCC)
unnamed: R403.2, U401.11 (CRS_DV/MODE2)
unnamed: J401.12, U401.3 (LED1/REGOFF)
unnamed: J401.9, R416.2, U401.2 (LED2/~INTSEL)
unnamed: R414.2, U401.24 (RBIAS)
unnamed: R401.2, R406.1, U401.8 (RXD0/MODE0)
unnamed: R402.2, R407.1, U401.7 (RXD1/MODE1)
unnamed: R410.2, U401.10 (RXER/PHYAD0)
unnamed: C404.1, C405.1, U401.6 (VDDCR)
unnamed: C401.2, U401.5 (XTAL1/CLKIN), Y401.3
unnamed: C402.2, U401.4 (XTAL2), Y401.1
unnamed: R404.2, R409.1, U401.14 (~INT/REFCLKO)
unnamed: R505.2, U501.2 (1A)
unnamed: R506.2, U501.1 (1B)
unnamed: R513.1, U501.3 (1Y)
unnamed: R507.2, U501.6 (2A)
unnamed: R508.2, U501.7 (2B)
unnamed: R514.1, U501.5 (2Y)
unnamed: R509.2, U501.10 (3A)
unnamed: R510.2, U501.9 (3B)
unnamed: R515.1, U501.11 (3Y)
unnamed: R511.2, U501.14 (4A)
unnamed: R512.2, U501.15 (4B)
unnamed: R516.1, U501.13 (4Y)
unnamed: R605.2, U601.2 (1A)
unnamed: R606.2, U601.1 (1B)
unnamed: R613.1, U601.3 (1Y)
unnamed: R607.2, U601.6 (2A)
unnamed: R608.2, U601.7 (2B)
unnamed: R614.1, U601.5 (2Y)
unnamed: R609.2, U601.10 (3A)
unnamed: R610.2, U601.9 (3B)
unnamed: R615.1, U601.11 (3Y)
unnamed: R611.2, U601.14 (4A)
unnamed: R612.2, U601.15 (4B)
unnamed: R616.1, U601.13 (4Y)
unnamed: R705.2, U701.2 (1A)
unnamed: R706.2, U701.1 (1B)
unnamed: R713.1, U701.3 (1Y)
unnamed: R707.2, U701.6 (2A)
unnamed: R708.2, U701.7 (2B)
unnamed: R714.1, U701.5 (2Y)
unnamed: R709.2, U701.10 (3A)
unnamed: R710.2, U701.9 (3B)
unnamed: R715.1, U701.11 (3Y)
unnamed: R711.2, U701.14 (4A)
unnamed: R712.2, U701.15 (4B)
unnamed: R716.1, U701.13 (4Y)
unnamed: R805.2, U801.2 (1A)
unnamed: R806.2, U801.1 (1B)
unnamed: R813.1, U801.3 (1Y)
unnamed: R807.2, U801.6 (2A)
unnamed: R808.2, U801.7 (2B)
unnamed: R814.1, U801.5 (2Y)
unnamed: R809.2, U801.10 (3A)
unnamed: R810.2, U801.9 (3B)
unnamed: R815.1, U801.11 (3Y)
unnamed: R811.2, U801.14 (4A)
unnamed: R812.2, U801.15 (4B)
unnamed: R816.1, U801.13 (4Y)
unnamed: R905.2, U901.2 (1A)
unnamed: R906.2, U901.1 (1B)
unnamed: R913.1, U901.3 (1Y)
unnamed: R907.2, U901.6 (2A)
unnamed: R908.2, U901.7 (2B)
unnamed: R914.1, U901.5 (2Y)
unnamed: R909.2, U901.10 (3A)
unnamed: R910.2, U901.9 (3B)
unnamed: R915.1, U901.11 (3Y)
unnamed: R911.2, U901.14 (4A)
unnamed: R912.2, U901.15 (4B)
unnamed: R916.1, U901.13 (4Y)
unnamed: R1005.2, U1001.2 (1A)
unnamed: R1006.2, U1001.1 (1B)
unnamed: R1013.1, U1001.3 (1Y)
unnamed: R1007.2, U1001.6 (2A)
unnamed: R1008.2, U1001.7 (2B)
unnamed: R1014.1, U1001.5 (2Y)
unnamed: R1009.2, U1001.10 (3A)
unnamed: R1010.2, U1001.9 (3B)
unnamed: R1015.1, U1001.11 (3Y)
unnamed: R1011.2, U1001.14 (4A)
unnamed: R1012.2, U1001.15 (4B)
unnamed: R1016.1, U1001.13 (4Y)
unnamed: R1105.2, U1101.2 (1A)
unnamed: R1106.2, U1101.1 (1B)
unnamed: R1113.1, U1101.3 (1Y)
unnamed: R1107.2, U1101.6 (2A)
unnamed: R1108.2, U1101.7 (2B)
unnamed: R1114.1, U1101.5 (2Y)
unnamed: R1109.2, U1101.10 (3A)
unnamed: R1110.2, U1101.9 (3B)
unnamed: R1115.1, U1101.11 (3Y)
unnamed: R1111.2, U1101.14 (4A)
unnamed: R1112.2, U1101.15 (4B)
unnamed: R1116.1, U1101.13 (4Y)
unnamed: R1205.2, U1201.2 (1A)
unnamed: R1206.2, U1201.1 (1B)
unnamed: R1213.1, U1201.3 (1Y)
unnamed: R1207.2, U1201.6 (2A)
unnamed: R1208.2, U1201.7 (2B)
unnamed: R1214.1, U1201.5 (2Y)
unnamed: R1209.2, U1201.10 (3A)
unnamed: R1210.2, U1201.9 (3B)
unnamed: R1215.1, U1201.11 (3Y)
unnamed: R1211.2, U1201.14 (4A)
unnamed: R1212.2, U1201.15 (4B)
unnamed: R1216.1, U1201.13 (4Y)
unnamed: R1305.2, U1301.2 (1A)
unnamed: R1306.2, U1301.1 (1B)
unnamed: R1313.1, U1301.3 (1Y)
unnamed: R1307.2, U1301.6 (2A)
unnamed: R1308.2, U1301.7 (2B)
unnamed: R1314.1, U1301.5 (2Y)
unnamed: R1309.2, U1301.10 (3A)
unnamed: R1310.2, U1301.9 (3B)
unnamed: R1315.1, U1301.11 (3Y)
unnamed: R1311.2, U1301.14 (4A)
unnamed: R1312.2, U1301.15 (4B)
unnamed: R1316.1, U1301.13 (4Y)
unnamed: R1405.2, U1401.1 (1A)
unnamed: R1409.1, U1401.2 (1Y)
unnamed: R1410.1, U1401.3 (1Z)
unnamed: R1406.2, U1401.7 (2A)
unnamed: R1411.1, U1401.6 (2Y)
unnamed: R1412.1, U1401.5 (2Z)
unnamed: R1407.2, U1401.9 (3A)
unnamed: R1413.1, U1401.10 (3Y)
unnamed: R1414.1, U1401.11 (3Z)
unnamed: R1408.2, U1401.15 (4A)
unnamed: R1415.1, U1401.14 (4Y)
unnamed: R1416.1, U1401.13 (4Z)
unnamed: R1505.2, U1501.1 (1A)
unnamed: R1509.1, U1501.2 (1Y)
unnamed: R1510.1, U1501.3 (1Z)
unnamed: R1506.2, U1501.7 (2A)
unnamed: R1511.1, U1501.6 (2Y)
unnamed: R1512.1, U1501.5 (2Z)
unnamed: R1507.2, U1501.9 (3A)
unnamed: R1513.1, U1501.10 (3Y)
unnamed: R1514.1, U1501.11 (3Z)
unnamed: R1508.2, U1501.15 (4A)
unnamed: R1515.1, U1501.14 (4Y)
unnamed: R1516.1, U1501.13 (4Z)
unnamed: R1605.2, U1601.1 (1A)
unnamed: R1609.1, U1601.2 (1Y)
unnamed: R1610.1, U1601.3 (1Z)
unnamed: R1606.2, U1601.7 (2A)
unnamed: R1611.1, U1601.6 (2Y)
unnamed: R1612.1, U1601.5 (2Z)
unnamed: R1607.2, U1601.9 (3A)
unnamed: R1613.1, U1601.10 (3Y)
unnamed: R1614.1, U1601.11 (3Z)
unnamed: R1608.2, U1601.15 (4A)
unnamed: R1615.1, U1601.14 (4Y)
unnamed: R1616.1, U1601.13 (4Z)
unnamed: R1705.2, U1701.1 (1A)
unnamed: R1709.1, U1701.2 (1Y)
unnamed: R1710.1, U1701.3 (1Z)
unnamed: R1706.2, U1701.7 (2A)
unnamed: R1711.1, U1701.6 (2Y)
unnamed: R1712.1, U1701.5 (2Z)
unnamed: R1707.2, U1701.9 (3A)
unnamed: R1713.1, U1701.10 (3Y)
unnamed: R1714.1, U1701.11 (3Z)
unnamed: R1708.2, U1701.15 (4A)
unnamed: R1715.1, U1701.14 (4Y)
unnamed: R1716.1, U1701.13 (4Z)
unnamed: R1805.2, U1801.1 (1A)
unnamed: R1809.1, U1801.2 (1Y)
unnamed: R1810.1, U1801.3 (1Z)
unnamed: R1806.2, U1801.7 (2A)
unnamed: R1811.1, U1801.6 (2Y)
unnamed: R1812.1, U1801.5 (2Z)
unnamed: R1807.2, U1801.9 (3A)
unnamed: R1813.1, U1801.10 (3Y)
unnamed: R1814.1, U1801.11 (3Z)
unnamed: R1808.2, U1801.15 (4A)
unnamed: R1815.1, U1801.14 (4Y)
unnamed: R1816.1, U1801.13 (4Z)
unnamed: R1905.2, U1901.1 (1A)
unnamed: R1909.1, U1901.2 (1Y)
unnamed: R1910.1, U1901.3 (1Z)
unnamed: R1906.2, U1901.7 (2A)
unnamed: R1911.1, U1901.6 (2Y)
unnamed: R1912.1, U1901.5 (2Z)
unnamed: R1907.2, U1901.9 (3A)
unnamed: R1913.1, U1901.10 (3Y)
unnamed: R1914.1, U1901.11 (3Z)
unnamed: R1908.2, U1901.15 (4A)
unnamed: R1915.1, U1901.14 (4Y)
unnamed: R1916.1, U1901.13 (4Z)
unnamed: R2005.2, U2001.1 (1A)
unnamed: R2009.1, U2001.2 (1Y)
unnamed: R2010.1, U2001.3 (1Z)
unnamed: R2006.2, U2001.7 (2A)
unnamed: R2011.1, U2001.6 (2Y)
unnamed: R2012.1, U2001.5 (2Z)
unnamed: R2007.2, U2001.9 (3A)
unnamed: R2013.1, U2001.10 (3Y)
unnamed: R2014.1, U2001.11 (3Z)
unnamed: R2008.2, U2001.15 (4A)
unnamed: R2015.1, U2001.14 (4Y)
unnamed: R2016.1, U2001.13 (4Z)
unnamed: R2105.2, U2101.1 (1A)
unnamed: R2109.1, U2101.2 (1Y)
unnamed: R2110.1, U2101.3 (1Z)
unnamed: R2106.2, U2101.7 (2A)
unnamed: R2111.1, U2101.6 (2Y)
unnamed: R2112.1, U2101.5 (2Z)
unnamed: R2107.2, U2101.9 (3A)
unnamed: R2113.1, U2101.10 (3Y)
unnamed: R2114.1, U2101.11 (3Z)
unnamed: R2108.2, U2101.15 (4A)
unnamed: R2115.1, U2101.14 (4Y)
unnamed: R2116.1, U2101.13 (4Z)
unnamed: R2205.2, U2201.1 (1A)
unnamed: R2209.1, U2201.2 (1Y)
unnamed: R2210.1, U2201.3 (1Z)
unnamed: R2206.2, U2201.7 (2A)
unnamed: R2211.1, U2201.6 (2Y)
unnamed: R2212.1, U2201.5 (2Z)
unnamed: R2207.2, U2201.9 (3A)
unnamed: R2213.1, U2201.10 (3Y)
unnamed: R2214.1, U2201.11 (3Z)
unnamed: R2208.2, U2201.15 (4A)
unnamed: R2215.1, U2201.14 (4Y)
unnamed: R2216.1, U2201.13 (4Z)
VDD: D301.2 (A2), F301.1, J301.1, J301.2
